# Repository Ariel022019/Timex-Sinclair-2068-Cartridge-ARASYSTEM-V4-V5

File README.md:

## :small_blue_diamond: Timex-Sinclair-2068-Cartridge-ARASYSTEM-V4-V5
This is a cartridge for Timex Sinclair 2068, to work with EPROMs 28C64, 27C128, 27C256, 27C512, EEPROMs 28C54, 28C256 and Static RAM 66256, 84256 and another with the same characteristics.  Using jumpers or mini switches, this PCB can be configured to get different settings.
With its unique design, there is no need to configure bridges to select fragments. The chunks can be configured by software.

### :small_blue_diamond: Jumpers configutation for each kind of EPROM /EEPROM

### :small_blue_diamond: Place right way to the socket the EPROM / EEPROM 

#### 🔸 Watch the creation of the first cartridge on video 
[Youtube Video Link](https://www.youtube.com/watch?v=S2ucEzxKyNs)

### 🔹 Cartridges With Mini Switches.
These mini switches allows to divide the EPROM memory into two or four parts, depending on the size of the EPROM (32k or 64K).

######  ▪️ ▪️ EPROM 27C256 divided into two 16K sizes

[See video example on Youtube](https://www.youtube.com/watch?v=SSa5LG2SbeI)

######  ▪️ ▪️ EPROM 27C512 divided into four 16K sizes

[See video example on Youtube](https://www.youtube.com/watch?v=w1bCyKRASG4)

######  ▪️ ▪️ Combining various configurations with switches and jumpers

### 🔹 Timex Sinclair 2068 Cartridge With 32K Static RAM 
This cartridge is used to expand 32K of RAM and store your own programs or data, which are stored in memory through a 3 Volt battery. Both the cartridge board and the battery holder board have their protection diodes, so as not to interfere with the voltages between them.
Commercial programs that start in AROS mode can also be stored. (Only one game at a time, eg Flight Simulator, Androids, Crazy Bugs, Casino 1 and others).
this system is that they can generate / experiment cartridges, without the need for burners and / or ERPOM erasers.

######  ▪️ ▪️ Battery connection.

######  ▪️ ▪️ Static RAM located in the socket.

######  ▪️ ▪️ Inserted inside the Dock Bank.

[Demo on Youtube](https://www.youtube.com/watch?v=_XW6AfT9foQ)

## 🔸 License.

######  UNDER LICENSE: CC BY NC ND 4.0
- You may not use the material for commercial purposes.

<a rel="license" href="http://creativecommons.org/licenses/by-nc-nd/4.0/">Attribution-NonCommercial-NoDerivatives 4.0 International</a><br />

#### 🔹 You can get these cartridges or more information:

Contact to: ariel.ranieri.sistemas@gmail.com

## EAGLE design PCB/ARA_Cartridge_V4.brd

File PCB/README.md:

# 🔹 Design for every need.

This cartridge can be setting according to the needs of the end user

## 🔹 Cartridge scheme to replace jumpers using a switch and a jumper.

###### ◾ EPROM 27C256 divided into two equal parts 16K in size

###### ◾ EPROM 27C512 divided into two equal parts 32K in size

## 🔹 Cartridge scheme to replace jumpers using two switch.

###### ◾ EPROM 27C512 divided into four equal parts 16K in size

## 🔸 Cartridge scheme to use static ram and battery.

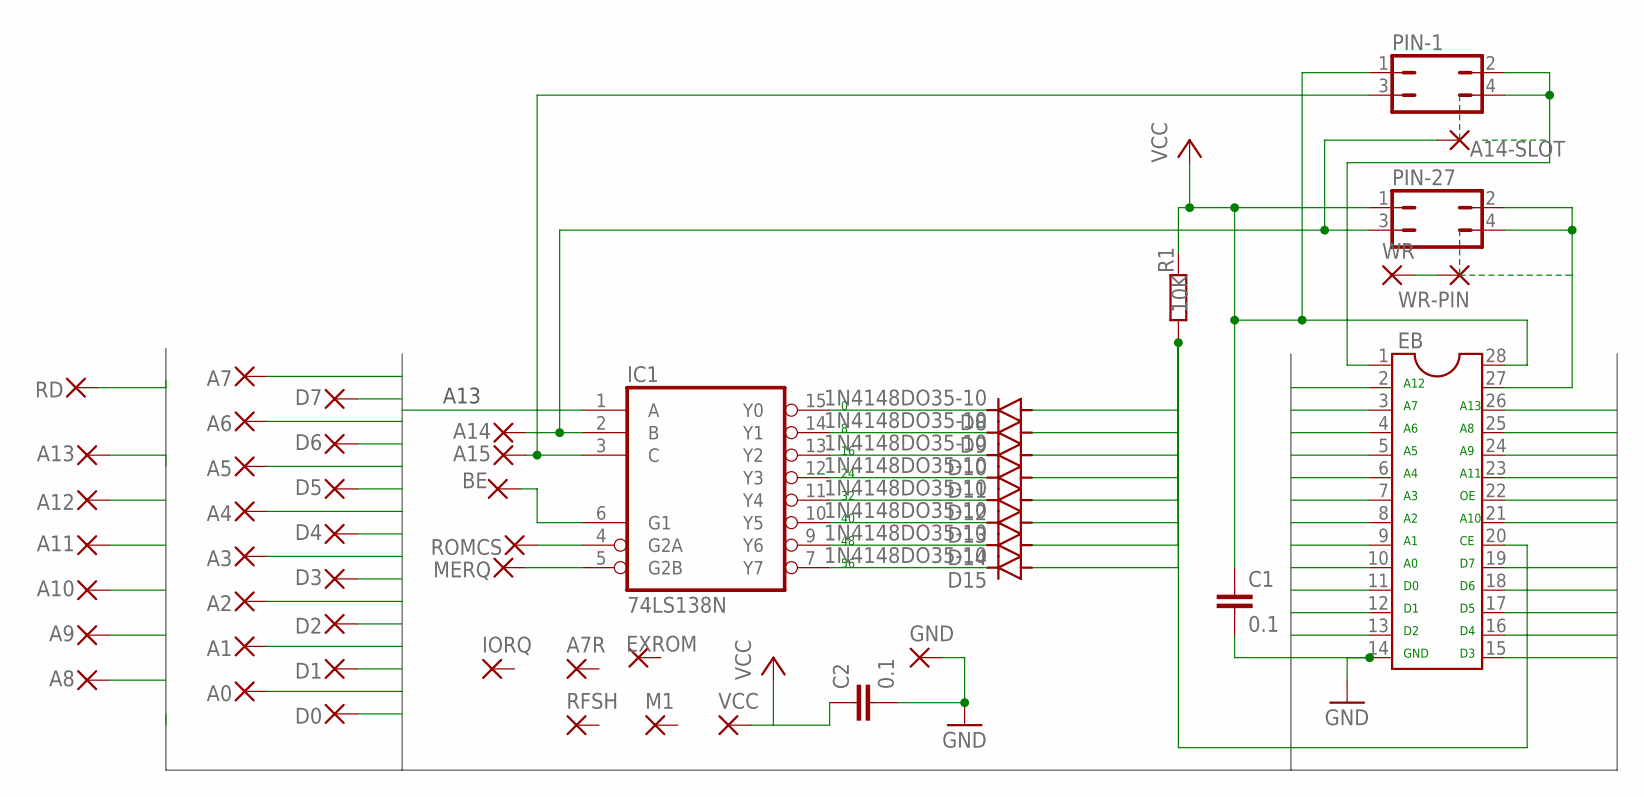
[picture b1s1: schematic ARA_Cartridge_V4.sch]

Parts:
A0, A1, A2, A3, A4, A5, A6, A7, A7R, A8, A9, A10, A11, A12, A13, A14, A15: SMD2
A14-SLOT: 1,6/0,8
BE: SMD2
C1, C2: 0.1; C2.5-3
D0, D1, D2, D3, D4, D5, D6, D7: SMD2
D8, D9, D10, D11, D12, D13, D14, D15: 1N4148DO35-10; DO35-10
EB: DIL28; DIL28-6
EXROM: SMD2
GND: SMD2
IC1: 74LS138N; DIL16
IORQ: SMD2
M1: SMD2
MERQ: SMD2
PIN-1, PIN-27: JP2Q
R1: 10K; 0207/10
RD: SMD2
RFSH: SMD2
ROMCS: SMD2
VCC: SMD2
WR: SMD2
WR-PIN: 1,6/0,8

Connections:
A0: A0.1, EB.10
A1: A1.1, EB.9
A2: A2.1, EB.8
A3: A3.1, EB.7
A4: A4.1, EB.6
A5: A5.1, EB.5
A6: A6.1, EB.4
A7: A7.1, EB.3
A8: A8.1, EB.25
A9: A9.1, EB.24
A10: A10.1, EB.21
A11: A11.1, EB.23
A12: A12.1, EB.2
A13: A13.1, EB.26, IC1.1 (A)
A14-EP: EB.27, PIN-27.2, PIN-27.4
A14-I: A14.1, A14-SLOT.1, IC1.2 (B), PIN-27.3
A15-EP: EB.1, PIN-1.2, PIN-1.4
A15-I: A15.1, IC1.3 (C), PIN-1.3
B0: D8.C, IC1.15 (Y0)
B1: D9.C, IC1.14 (Y1)
B2: D10.C, IC1.13 (Y2)
B3: D11.C, IC1.12 (Y3)
B4: D12.C, IC1.11 (Y4)
B5: D13.C, IC1.10 (Y5)
B6: D14.C, IC1.9 (Y6)
B7: D15.C, IC1.7 (Y7)
BE: BE.1, IC1.6 (G1)
D0: D0.1, EB.11
D1: D1.1, EB.12
D2: D2.1, EB.13
D3: D3.1, EB.15
D4: D4.1, EB.16
D5: D5.1, EB.17
D6: D6.1, EB.18
D7: D7.1, EB.19
GND: C1.2, C2.2, EB.14, GND.1, IC1.8 (GND)
unnamed: D8.A, D9.A, D10.A, D11.A, D12.A, D13.A, D14.A, D15.A, EB.20, R1.2
unnamed: IC1.5 (G2B), MERQ.1
unnamed: IC1.4 (G2A), ROMCS.1
RD: EB.22, RD.1
VCC: C1.1, C2.1, EB.28, IC1.16 (VCC), PIN-1.1, PIN-27.1, R1.1, VCC.1
WR: WR.1, WR-PIN.1

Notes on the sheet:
A13
A12
GND
A10
A11

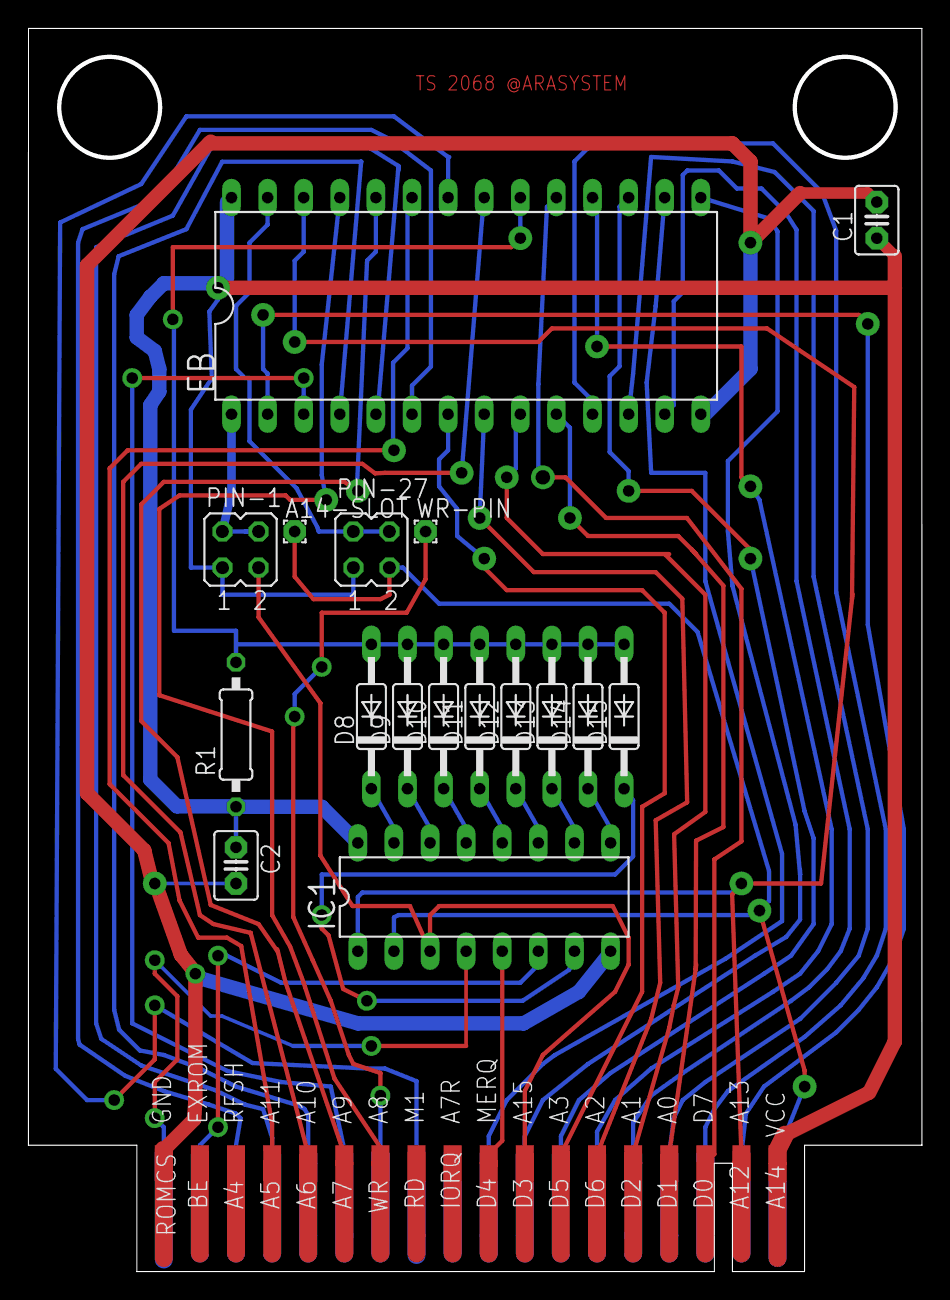
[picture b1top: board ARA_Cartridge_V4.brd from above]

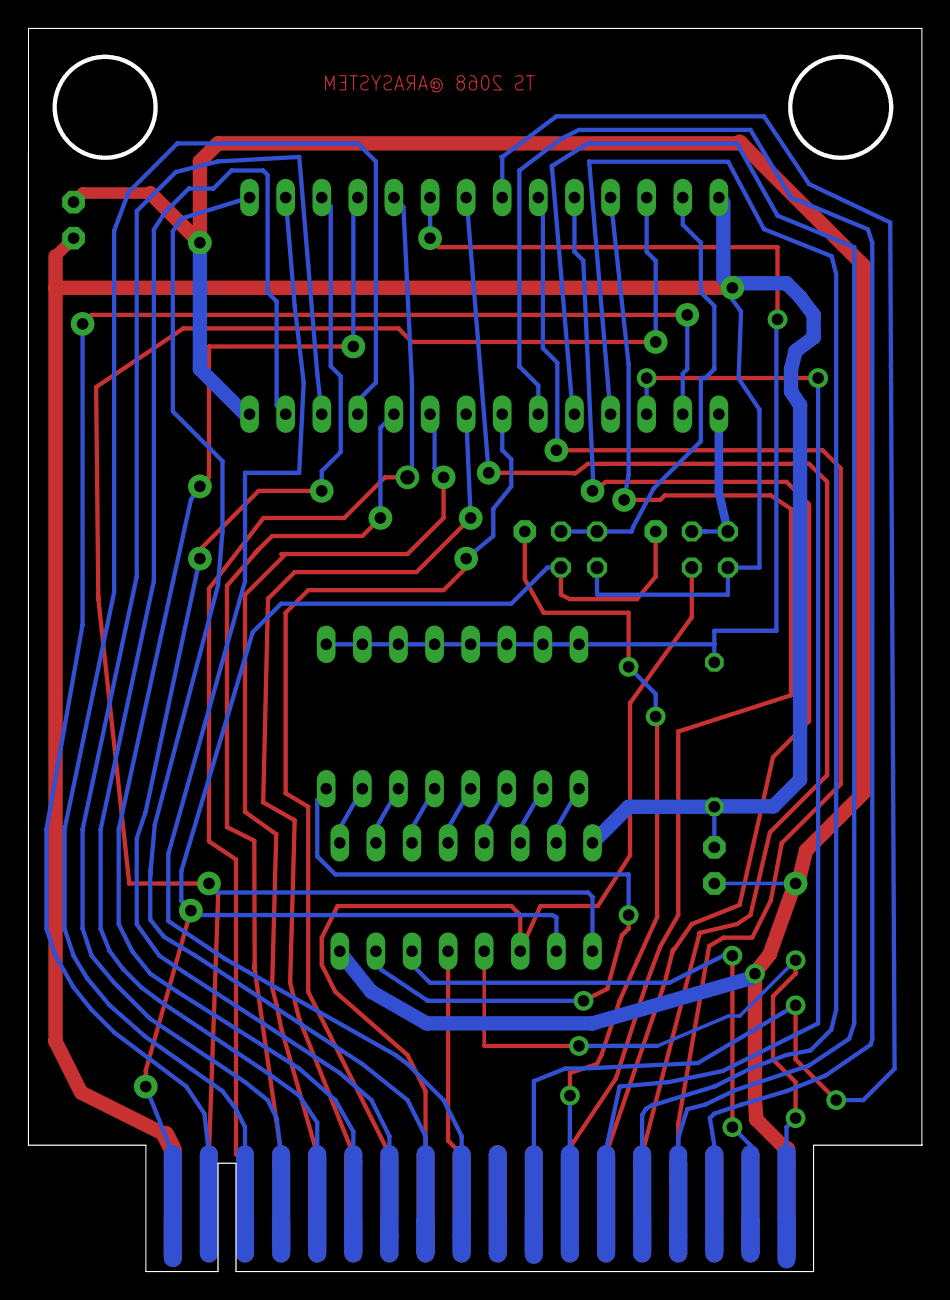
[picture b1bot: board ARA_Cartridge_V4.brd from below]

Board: 2 copper layers, 62.6 x 87.2 mm, 53 parts (18 on the bottom side), 42 nets.

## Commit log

2021-08-12 Rename info.md to README.md
2022-10-20 Create Schemes
